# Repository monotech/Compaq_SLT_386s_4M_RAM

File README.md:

# Compaq SLT 386s/20 4MiB RAM Module

Can be used alongside original modules.

The DRAM chips are obsolete and need to be purchased from the grey market.

The example part numbers below are just examples. There are many compatible chips from different brands with quite different part numbers. Compare datasheets.

Original modules used 80ns chips, so acquire chips that are 80ns or faster. I used 60ns just fine. Beware of fake/bad parts.

It's best to order with ENIG surface finish rather than HASL. If you'll be replugging it over a hundred times, selective 30u" hard-gold plating is recommended.

## Bill of materials
Designator|Part
---|---
U1-2,U4-5,U7-8,U10-11|1M*4 DRAM SOJ-20(26-size) or TSOP-II such as HY514400ALJ-60
U3,U6,U9,U12|1M*1 DRAM SOJ-20(26-size) or TSOP-II such as HY531000ALJ-50
U13-14|74AHC541 TSSOP-20
C1|10uF 0805
C2-9|100nF 0603
R1-14|33 ohm 0603

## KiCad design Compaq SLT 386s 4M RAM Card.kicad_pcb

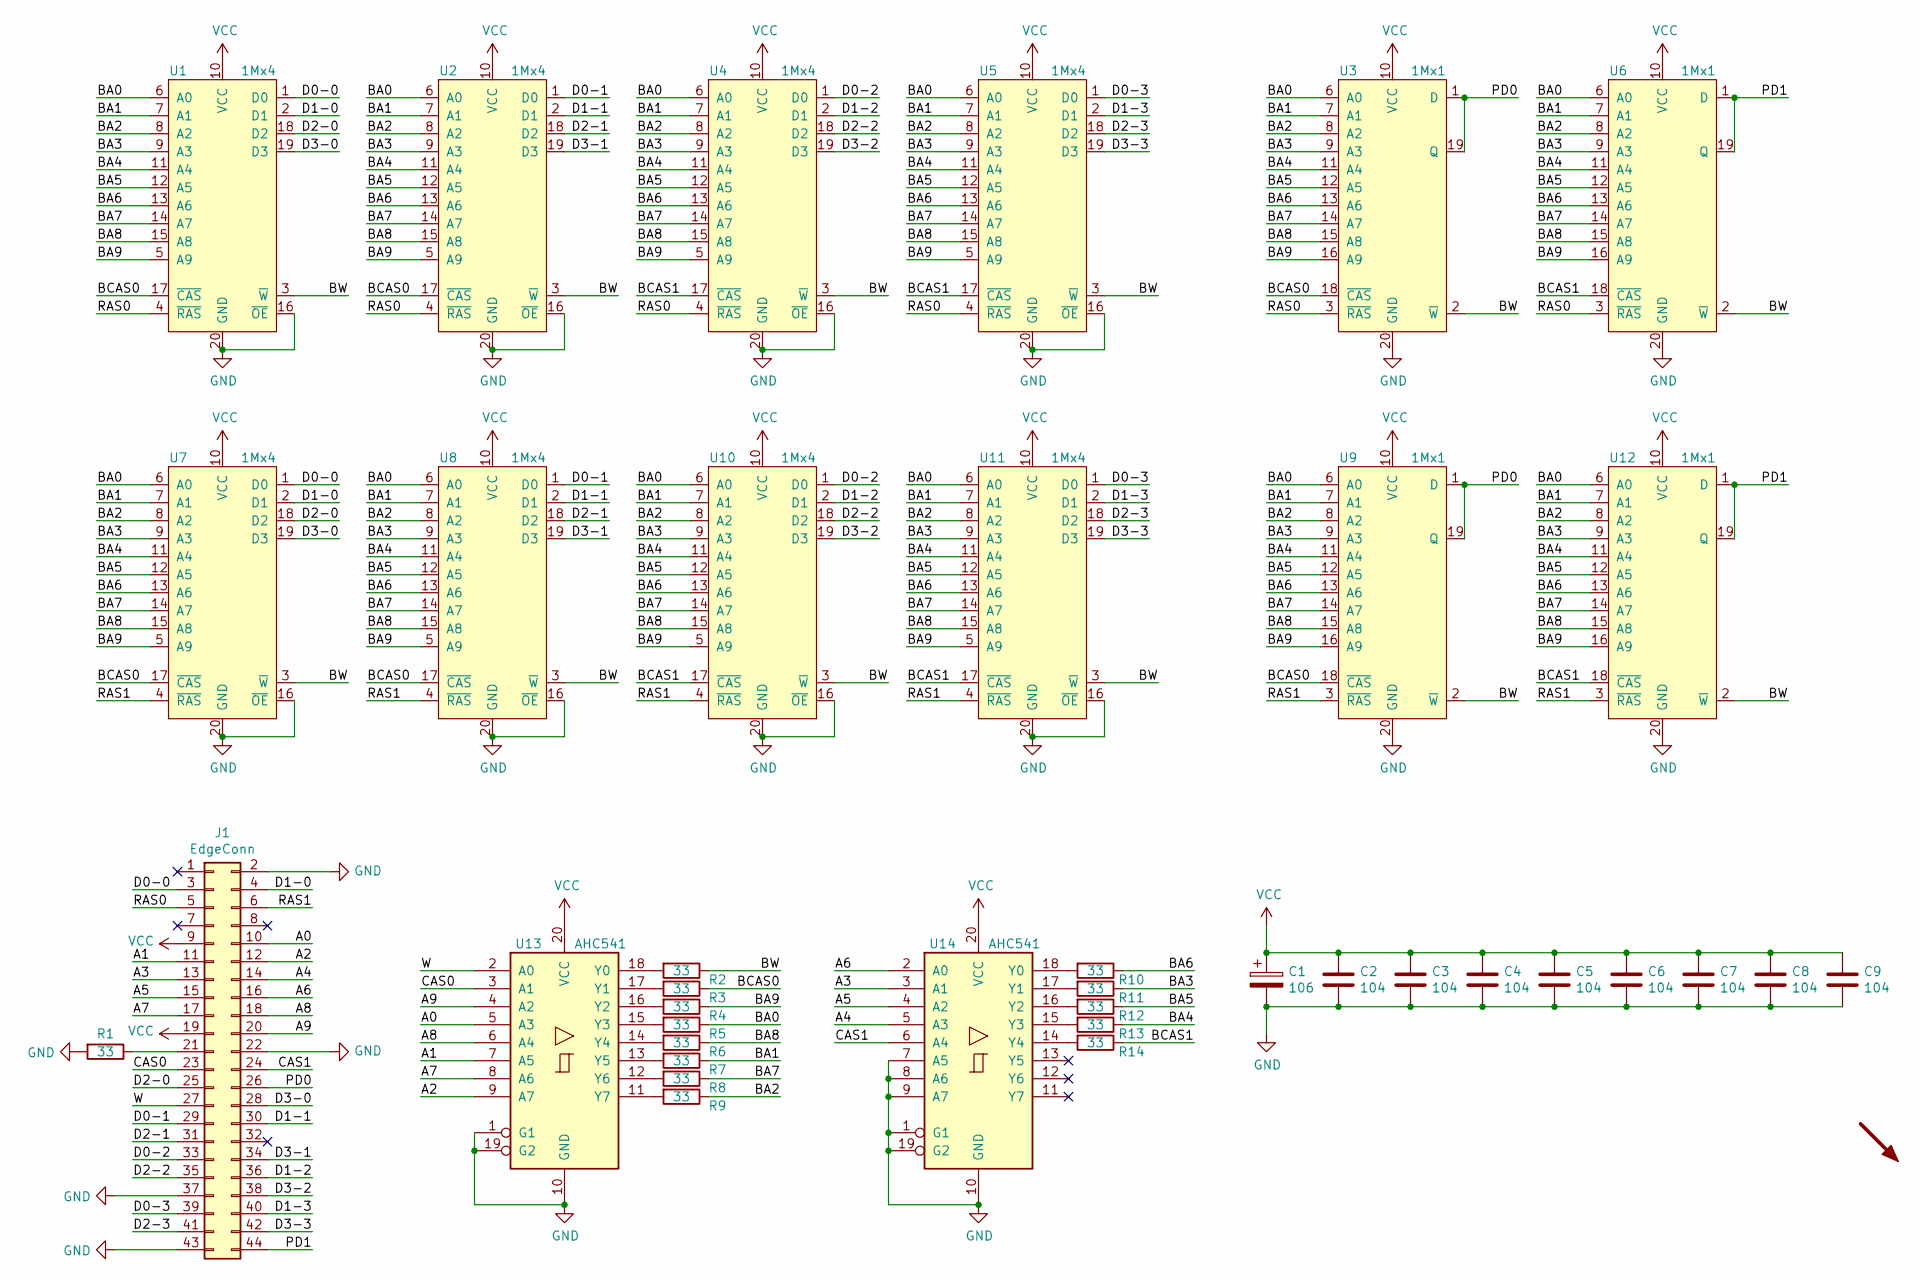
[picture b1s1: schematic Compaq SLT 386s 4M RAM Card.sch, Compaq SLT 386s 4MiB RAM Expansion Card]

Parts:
C1: 106; C_0805_2012Metric
C2, C3, C4, C5, C6, C7, C8, C9: 104; C_0603_1608Metric
J1: EdgeConn; Compaq_SLT386_RAM
LOGO1: LOGO; Monotech Logo 12mm
R1, R2, R3, R4, R5, R6, R7, R8, R9, R10, R11, R12, R13, R14: 33; R_0603_1608Metric
U1, U2, U4, U5, U7, U8, U10, U11: 1Mx4; TSOP-II_or_SOJ-26-20
U3, U6, U9, U12: 1Mx1; TSOP-II_or_SOJ-26-20
U13, U14: AHC541; TSSOP-20_4.4x6.5mm_P0.65mm

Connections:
/A0: J1.10, U13.5 (A3)
/A1: J1.11, U13.7 (A5)
/A2: J1.12, U13.9 (A7)
/A3: J1.13, U14.3 (A1)
/A4: J1.14, U14.5 (A3)
/A5: J1.15, U14.4 (A2)
/A6: J1.16, U14.2 (A0)
/A7: J1.17, U13.8 (A6)
/A8: J1.18, U13.6 (A4)
/A9: J1.20, U13.4 (A2)
/BA0: R5.1, U1.6 (A0), U2.6 (A0), U3.6 (A0), U4.6 (A0), U5.6 (A0), U6.6 (A0), U7.6 (A0), U8.6 (A0), U9.6 (A0), U10.6 (A0), U11.6 (A0), U12.6 (A0)
/BA1: R7.1, U1.7 (A1), U2.7 (A1), U3.7 (A1), U4.7 (A1), U5.7 (A1), U6.7 (A1), U7.7 (A1), U8.7 (A1), U9.7 (A1), U10.7 (A1), U11.7 (A1), U12.7 (A1)
/BA2: R9.1, U1.8 (A2), U2.8 (A2), U3.8 (A2), U4.8 (A2), U5.8 (A2), U6.8 (A2), U7.8 (A2), U8.8 (A2), U9.8 (A2), U10.8 (A2), U11.8 (A2), U12.8 (A2)
/BA3: R11.1, U1.9 (A3), U2.9 (A3), U3.9 (A3), U4.9 (A3), U5.9 (A3), U6.9 (A3), U7.9 (A3), U8.9 (A3), U9.9 (A3), U10.9 (A3), U11.9 (A3), U12.9 (A3)
/BA4: R13.1, U1.11 (A4), U2.11 (A4), U3.11 (A4), U4.11 (A4), U5.11 (A4), U6.11 (A4), U7.11 (A4), U8.11 (A4), U9.11 (A4), U10.11 (A4), U11.11 (A4), U12.11 (A4)
/BA5: R12.1, U1.12 (A5), U2.12 (A5), U3.12 (A5), U4.12 (A5), U5.12 (A5), U6.12 (A5), U7.12 (A5), U8.12 (A5), U9.12 (A5), U10.12 (A5), U11.12 (A5), U12.12 (A5)
/BA6: R10.1, U1.13 (A6), U2.13 (A6), U3.13 (A6), U4.13 (A6), U5.13 (A6), U6.13 (A6), U7.13 (A6), U8.13 (A6), U9.13 (A6), U10.13 (A6), U11.13 (A6), U12.13 (A6)
/BA7: R8.1, U1.14 (A7), U2.14 (A7), U3.14 (A7), U4.14 (A7), U5.14 (A7), U6.14 (A7), U7.14 (A7), U8.14 (A7), U9.14 (A7), U10.14 (A7), U11.14 (A7), U12.14 (A7)
/BA8: R6.1, U1.15 (A8), U2.15 (A8), U3.15 (A8), U4.15 (A8), U5.15 (A8), U6.15 (A8), U7.15 (A8), U8.15 (A8), U9.15 (A8), U10.15 (A8), U11.15 (A8), U12.15 (A8)
/BA9: R4.1, U1.5 (A9), U2.5 (A9), U3.16 (A9), U4.5 (A9), U5.5 (A9), U6.16 (A9), U7.5 (A9), U8.5 (A9), U9.16 (A9), U10.5 (A9), U11.5 (A9), U12.16 (A9)
/BCAS0: R3.1, U1.17 (~CAS), U2.17 (~CAS), U3.18 (~CAS), U7.17 (~CAS), U8.17 (~CAS), U9.18 (~CAS)
/BCAS1: R14.1, U4.17 (~CAS), U5.17 (~CAS), U6.18 (~CAS), U10.17 (~CAS), U11.17 (~CAS), U12.18 (~CAS)
/BW: R2.1, U1.3 (~W), U2.3 (~W), U3.2 (~W), U4.3 (~W), U5.3 (~W), U6.2 (~W), U7.3 (~W), U8.3 (~W), U9.2 (~W), U10.3 (~W), U11.3 (~W), U12.2 (~W)
/CAS0: J1.23, U13.3 (A1)
/CAS1: J1.24, U14.6 (A4)
/D0-0: J1.3, U1.1 (D0), U7.1 (D0)
/D0-1: J1.29, U2.1 (D0), U8.1 (D0)
/D0-2: J1.33, U4.1 (D0), U10.1 (D0)
/D0-3: J1.39, U5.1 (D0), U11.1 (D0)
/D1-0: J1.4, U1.2 (D1), U7.2 (D1)
/D1-1: J1.30, U2.2 (D1), U8.2 (D1)
/D1-2: J1.36, U4.2 (D1), U10.2 (D1)
/D1-3: J1.40, U5.2 (D1), U11.2 (D1)
/D2-0: J1.25, U1.18 (D2), U7.18 (D2)
/D2-1: J1.31, U2.18 (D2), U8.18 (D2)
/D2-2: J1.35, U4.18 (D2), U10.18 (D2)
/D2-3: J1.41, U5.18 (D2), U11.18 (D2)
/D3-0: J1.28, U1.19 (D3), U7.19 (D3)
/D3-1: J1.34, U2.19 (D3), U8.19 (D3)
/D3-2: J1.38, U4.19 (D3), U10.19 (D3)
/D3-3: J1.42, U5.19 (D3), U11.19 (D3)
/PD0: J1.26, U3.1 (D), U3.19 (Q), U9.1 (D), U9.19 (Q)
/PD1: J1.44, U6.1 (D), U6.19 (Q), U12.1 (D), U12.19 (Q)
/RAS0: J1.5, U1.4 (~RAS), U2.4 (~RAS), U3.3 (~RAS), U4.4 (~RAS), U5.4 (~RAS), U6.3 (~RAS)
/RAS1: J1.6, U7.4 (~RAS), U8.4 (~RAS), U9.3 (~RAS), U10.4 (~RAS), U11.4 (~RAS), U12.3 (~RAS)
/W: J1.27, U13.2 (A0)
GND: C1.2, C2.2, C3.2, C4.2, C5.2, C6.2, C7.2, C8.2, C9.2, J1.2, J1.22, J1.37, J1.43, R1.2, U1.16 (~OE), U1.20 (GND), U2.16 (~OE), U2.20 (GND), U3.20 (GND), U4.16 (~OE), U4.20 (GND), U5.16 (~OE), U5.20 (GND), U6.20 (GND), U7.16 (~OE), U7.20 (GND), U8.16 (~OE), U8.20 (GND), U9.20 (GND), U10.16 (~OE), U10.20 (GND), U11.16 (~OE), U11.20 (GND), U12.20 (GND), U13.1 (G1), U13.10 (GND), U13.19 (G2), U14.1 (G1), U14.7 (A5), U14.8 (A6), U14.9 (A7), U14.10 (GND), U14.19 (G2)
unnamed: J1.21, R1.1
unnamed: R2.2, U13.18 (Y0)
unnamed: R3.2, U13.17 (Y1)
unnamed: R4.2, U13.16 (Y2)
unnamed: R5.2, U13.15 (Y3)
unnamed: R6.2, U13.14 (Y4)
unnamed: R7.2, U13.13 (Y5)
unnamed: R8.2, U13.12 (Y6)
unnamed: R9.2, U13.11 (Y7)
unnamed: R10.2, U14.18 (Y0)
unnamed: R11.2, U14.17 (Y1)
unnamed: R12.2, U14.16 (Y2)
unnamed: R13.2, U14.15 (Y3)
unnamed: R14.2, U14.14 (Y4)
VCC: C1.1, C2.1, C3.1, C4.1, C5.1, C6.1, C7.1, C8.1, C9.1, J1.9, J1.19, U1.10 (VCC), U2.10 (VCC), U3.10 (VCC), U4.10 (VCC), U5.10 (VCC), U6.10 (VCC), U7.10 (VCC), U8.10 (VCC), U9.10 (VCC), U10.10 (VCC), U11.10 (VCC), U12.10 (VCC), U13.20 (VCC), U14.20 (VCC)

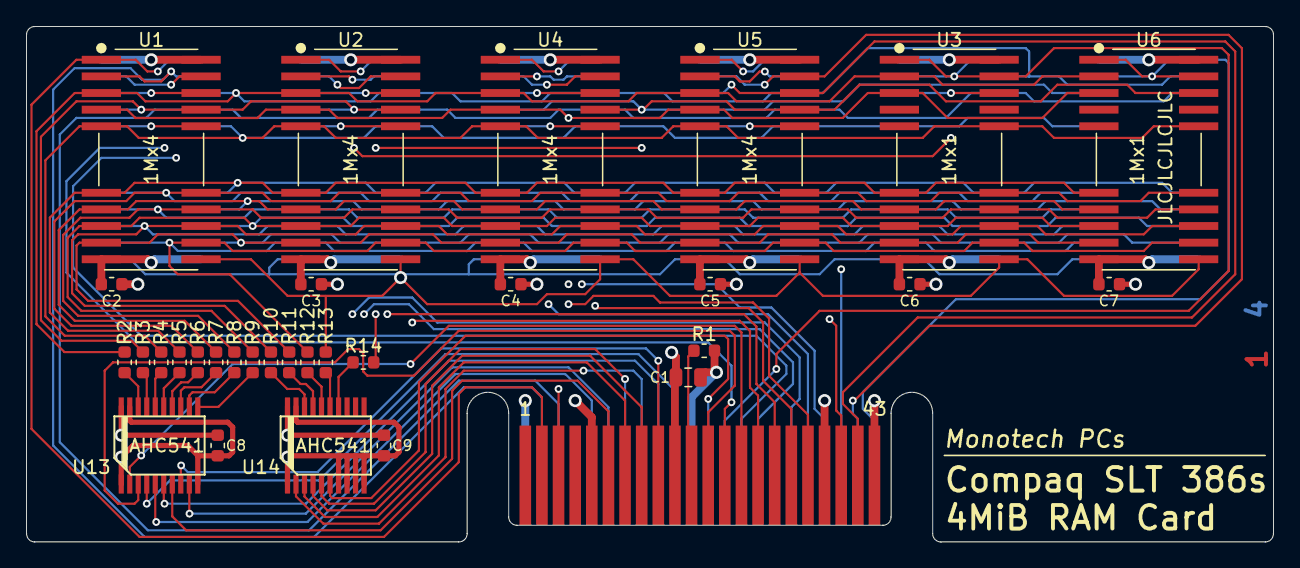
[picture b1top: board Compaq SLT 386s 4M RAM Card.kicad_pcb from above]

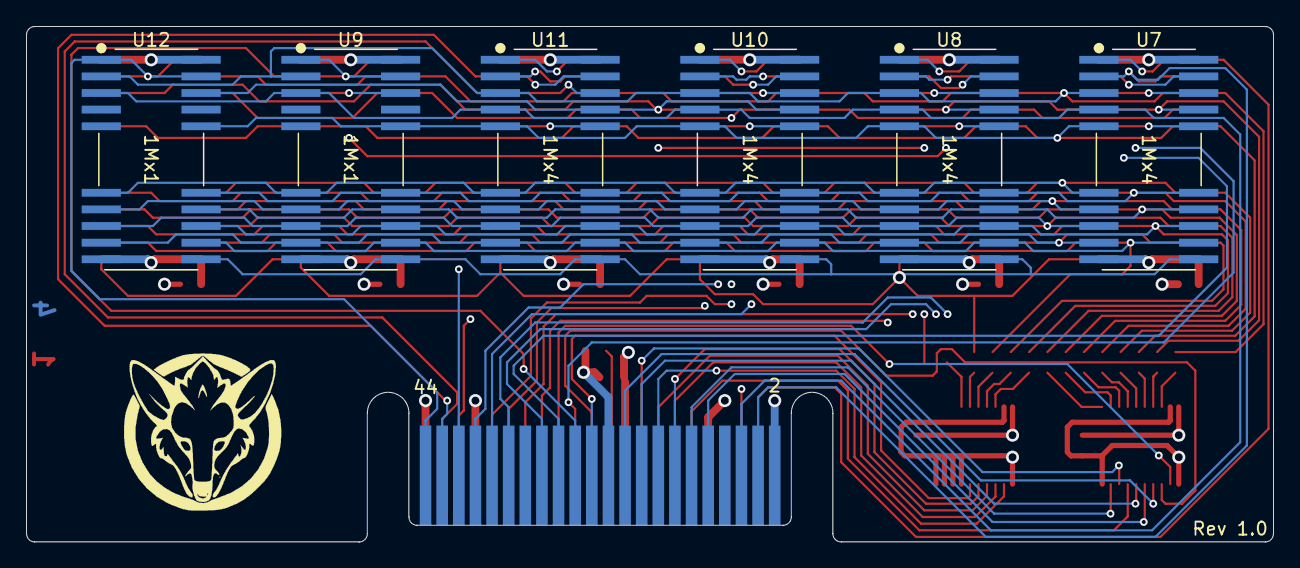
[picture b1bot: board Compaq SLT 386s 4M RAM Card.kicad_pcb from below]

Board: 4 copper layers, 95.2 x 39.4 mm, 39 parts (7 on the bottom side), 62 nets.
